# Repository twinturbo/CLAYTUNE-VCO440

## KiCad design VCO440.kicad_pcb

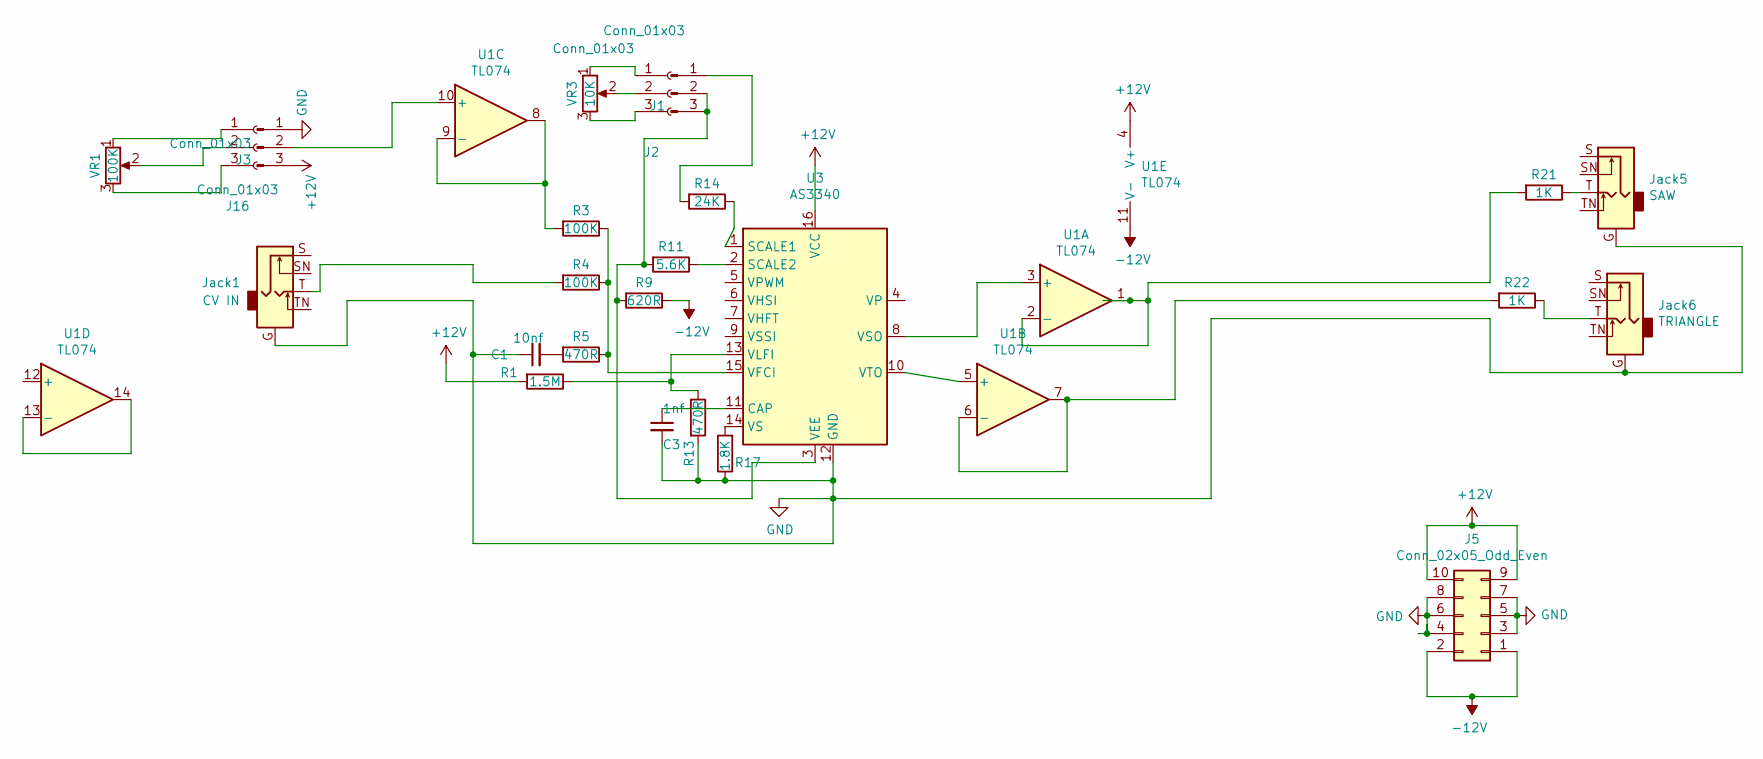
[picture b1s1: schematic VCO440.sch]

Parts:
C1: 10nf; C_Disc_D3.8mm_W2.6mm_P2.50mm
C3: 1nf; C_Disc_D3.8mm_W2.6mm_P2.50mm
J1, J3: Conn_01x03; PinHeader_1x03_P2.54mm_Vertical
J2, J16: Conn_01x03; PinSocket_1x03_P2.54mm_Vertical
J5: Conn_02x05_Odd_Even; IDC-Header_2x05_P2.54mm_Vertical
Jack1: CV IN; Jack_6.5mmLMNC
Jack5: SAW; Jack_6.5mmLMNC
Jack6: TRIANGLE; Jack_6.5mmLMNC
R1: 1.5M; R_Axial_DIN0207_L6.3mm_D2.5mm_P7.62mm_Horizontal
R3, R4: 100K; R_Axial_DIN0207_L6.3mm_D2.5mm_P7.62mm_Horizontal
R5, R13: 470R; R_Axial_DIN0207_L6.3mm_D2.5mm_P7.62mm_Horizontal
R9: 620R; R_Axial_DIN0207_L6.3mm_D2.5mm_P7.62mm_Horizontal
R11: 5.6K; R_Axial_DIN0207_L6.3mm_D2.5mm_P7.62mm_Horizontal
R14: 24K; R_Axial_DIN0207_L6.3mm_D2.5mm_P7.62mm_Horizontal
R17: 1.8K; R_Axial_DIN0207_L6.3mm_D2.5mm_P7.62mm_Horizontal
R21, R22: 1K; R_Axial_DIN0207_L6.3mm_D2.5mm_P7.62mm_Horizontal
U1: TL074; DIP-14_W7.62mm
U3: AS3340; DIP-16_W7.62mm_Socket
VR1: 100K; Potentiometer_Alps_RK09K_Single_Vertical
VR3: 10K; Potentiometer_Bourns_3296W_Vertical

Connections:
+12V: J3.3, J5.9, J5.10, R1.2, U1.4 (V+), U3.16 (VCC)
-12V: J5.1, J5.2, R9.1, U1.11 (V-)
GND: C1.1, C3.2, J3.1, J5.3, J5.4, J5.5, J5.6, J5.7, J5.8, Jack1.G, Jack5.G, Jack6.G, R13.2, R17.1, U3.12 (GND)
unnamed: C1.2, R5.2
unnamed: C3.1, U3.11 (CAP)
unnamed: J1.1, R14.2
unnamed: J1.2, J1.3, R9.2, R11.2, U3.3 (VEE)
unnamed: J2.1, VR3.1
unnamed: J2.2, VR3.2
unnamed: J2.3, VR3.3
unnamed: J3.2, U1.10 (+)
unnamed: J16.1, VR1.1
unnamed: J16.2, VR1.2
unnamed: J16.3, VR1.3
unnamed: Jack1.T, R4.2
unnamed: Jack5.T, R21.1
unnamed: Jack6.T, R22.1
unnamed: R1.1, R13.1, U3.13 (VLFI)
unnamed: R3.1, R4.1, R5.1, U3.15 (VFCI)
unnamed: R3.2, U1.8, U1.9 (-)
unnamed: R11.1, U3.2 (SCALE2)
unnamed: R14.1, U3.1 (SCALE1)
unnamed: R17.2, U3.14 (VS)
unnamed: R21.2, U1.1, U1.2 (-)
unnamed: R22.2, U1.6 (-), U1.7
unnamed: U1.3 (+), U3.8 (VSO)
unnamed: U1.5 (+), U3.10 (VTO)
unnamed: U1.13 (-), U1.14

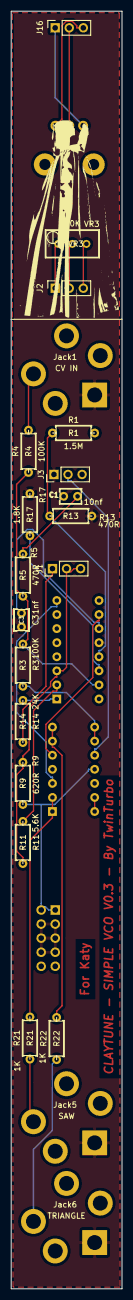
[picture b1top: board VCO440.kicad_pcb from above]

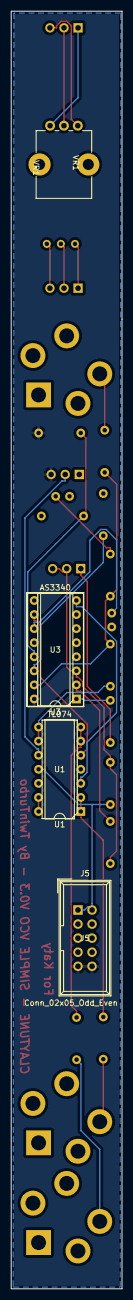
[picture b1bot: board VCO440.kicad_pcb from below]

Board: 2 copper layers, 20.0 x 230.6 mm, 26 parts (4 on the bottom side), 28 nets.

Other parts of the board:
G2: LOGO; GSIMG

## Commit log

2020-12-05 init
2020-12-05 tidy1
2020-12-05 Changelog
2020-12-05 autosync
2020-12-05 Board Version Number Changed to V0.2 from old Version V1.0
2020-12-26 Tidy
